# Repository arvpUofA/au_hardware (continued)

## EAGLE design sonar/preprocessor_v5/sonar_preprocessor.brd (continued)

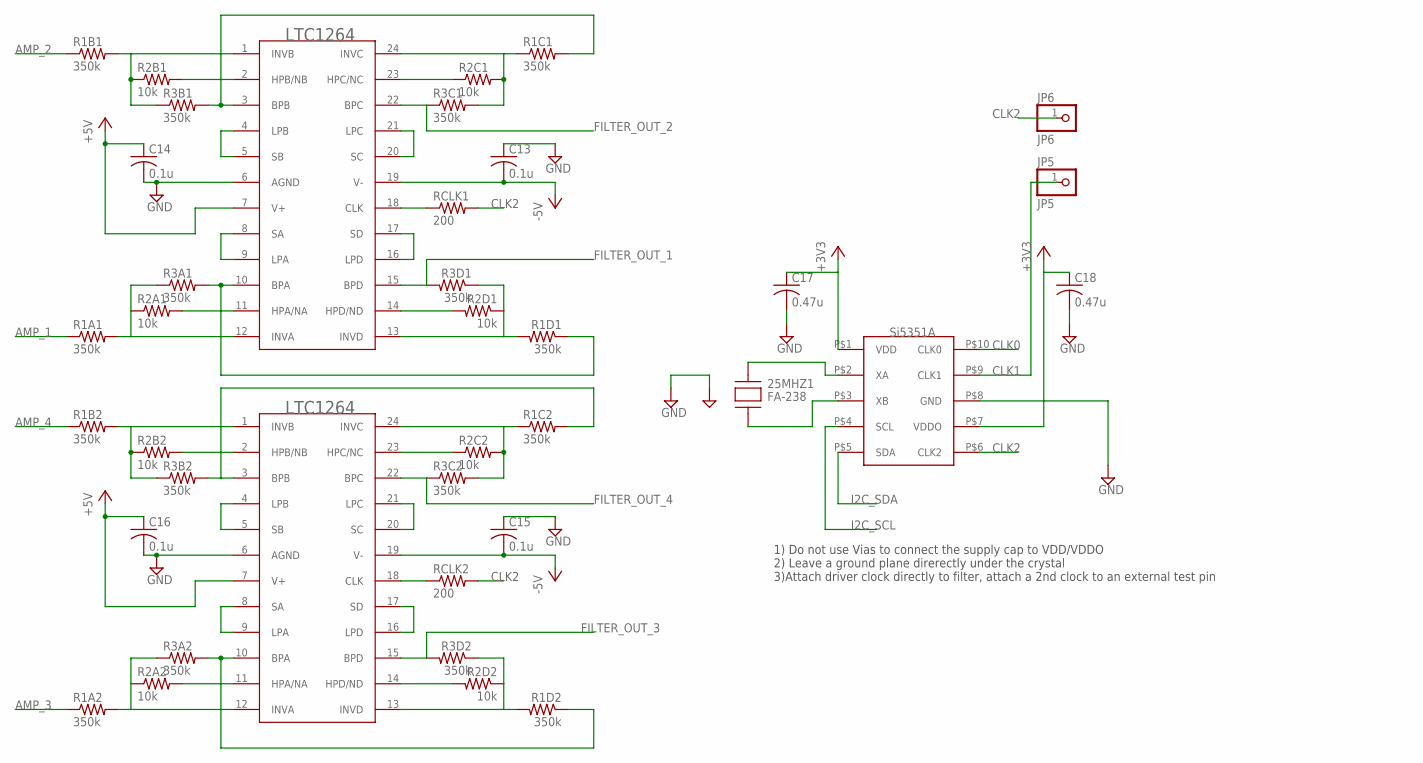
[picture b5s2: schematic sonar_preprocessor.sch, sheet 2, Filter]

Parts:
25MHZ1: FA-238
C13, C14, C15, C16: 0.1u; C0805
C17, C18: 0.47u; C0805
JP5: JP5; 1X01
JP6: JP6; 1X01
R1A1, R1A2, R1B1, R1B2, R1C1, R1C2, R1D1, R1D2, R3A1, R3A2, R3B1, R3B2, R3C1, R3C2, R3D1, R3D2: 350k; R0805
R2A1, R2A2, R2B1, R2B2, R2C1, R2C2, R2D1, R2D2: 10k; R0805
RCLK1, RCLK2: 200; R0805
U$6, U$7: LTC1264SMD; SO24W
U$8: SI5351A; MSOP-10

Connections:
+3V3: C17.1, C18.1, U$8.P$1 (VDD), U$8.P$7 (VDDO); also elsewhere on the board
+5V: C14.1, C16.1, U$6.7 (V+), U$7.7 (V+); also elsewhere on the board
-5V: C13.2, C15.2, U$6.19 (V-), U$7.19 (V-); also elsewhere on the board
AMP_1: R1A1.1; also elsewhere on the board
AMP_2: R1B1.1; also elsewhere on the board
AMP_3: R1A2.1; also elsewhere on the board
AMP_4: R1B2.1; also elsewhere on the board
CLK0: U$8.P$10 (CLK0)
CLK1: JP5.1, U$8.P$9 (CLK1)
CLK2: JP6.1, RCLK1.2, RCLK2.2, U$8.P$6 (CLK2)
FILTER_OUT_1: R3D1.2, U$6.15 (BPD); also elsewhere on the board
FILTER_OUT_2: R3C1.1, U$6.22 (BPC); also elsewhere on the board
FILTER_OUT_3: R3D2.2, U$7.15 (BPD); also elsewhere on the board
FILTER_OUT_4: R3C2.1, U$7.22 (BPC); also elsewhere on the board
GND: 25MHZ1.P$1 (GND), 25MHZ1.P$3 (GND), C13.1, C14.2, C15.1, C16.2, C17.2, C18.2, U$6.6 (AGND), U$7.6 (AGND), U$8.P$8 (GND); also elsewhere on the board
I2C_SCL: U$8.P$4 (SCL); also elsewhere on the board
I2C_SDA: U$8.P$5 (SDA); also elsewhere on the board
unnamed: U$7.20 (SC), U$7.21 (LPC)
unnamed: 25MHZ1.P$4 (XA), U$8.P$2 (XA)
unnamed: 25MHZ1.P$2 (XB), U$8.P$3 (XB)
unnamed: R2A1.2, U$6.11 (HPA/NA)
unnamed: U$6.8 (SA), U$6.9 (LPA)
unnamed: R1A1.2, R2A1.1, R3A1.1, U$6.12 (INVA)
unnamed: R2D1.2, U$6.14 (HPD/ND)
unnamed: R1D1.2, R2D1.1, R3D1.1, U$6.13 (INVD)
unnamed: U$6.16 (LPD), U$6.17 (SD)
unnamed: R2C1.1, U$6.23 (HPC/NC)
unnamed: R1C1.1, R2C1.2, R3C1.2, U$6.24 (INVC)
unnamed: R2C2.1, U$7.23 (HPC/NC)
unnamed: R2B1.2, U$6.2 (HPB/NB)
unnamed: R1B1.2, R2B1.1, R3B1.1, U$6.1 (INVB)
unnamed: U$6.4 (LPB), U$6.5 (SB)
unnamed: U$6.20 (SC), U$6.21 (LPC)
unnamed: RCLK1.1, U$6.18 (CLK)
unnamed: R2A2.2, U$7.11 (HPA/NA)
unnamed: U$7.8 (SA), U$7.9 (LPA)
unnamed: R1A2.2, R2A2.1, R3A2.1, U$7.12 (INVA)
unnamed: R2D2.2, U$7.14 (HPD/ND)
unnamed: R1D2.2, R2D2.1, R3D2.1, U$7.13 (INVD)
unnamed: U$7.16 (LPD), U$7.17 (SD)
unnamed: R1C2.1, R2C2.2, R3C2.2, U$7.24 (INVC)
unnamed: R2B2.2, U$7.2 (HPB/NB)
unnamed: R1B2.2, R2B2.1, R3B2.1, U$7.1 (INVB)
unnamed: U$7.4 (LPB), U$7.5 (SB)
unnamed: RCLK2.1, U$7.18 (CLK)
OUT_2ND_A1: R1D1.1, R3A1.2, U$6.10 (BPA)
OUT_2ND_A2: R1D2.1, R3A2.2, U$7.10 (BPA)
OUT_2ND_B2: R1C2.2, R3B2.2, U$7.3 (BPB)
OUT_2ND_ORDER_B1: R1C1.2, R3B1.2, U$6.3 (BPB)

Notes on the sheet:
1) Do not use Vias to connect the supply cap to VDD/VDDO 2) Leave a ground plane direrectly under the crystal 3)Attach driver clock directly to filter, attach a 2nd clock to an external test pin

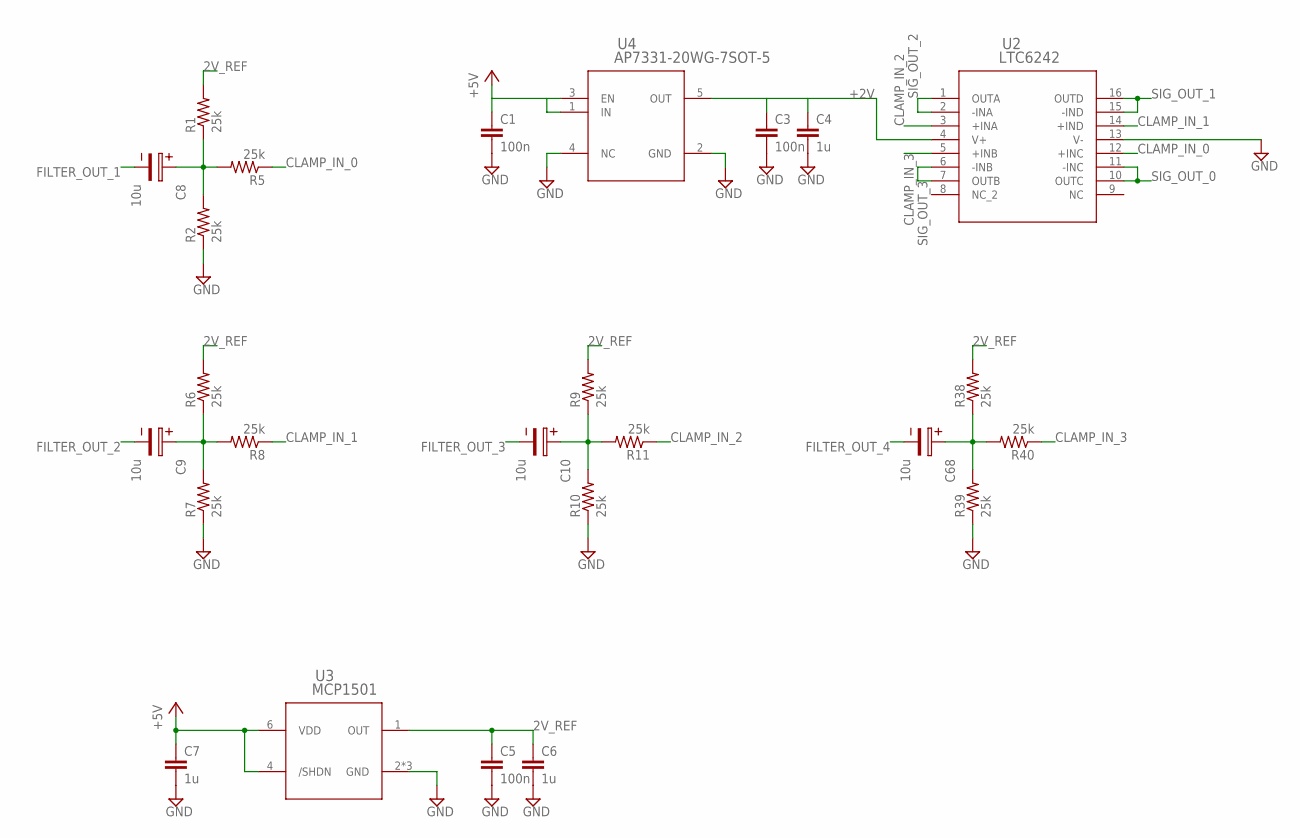
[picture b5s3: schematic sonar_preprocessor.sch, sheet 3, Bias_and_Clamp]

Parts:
C1, C3, C5: 100n; C0805
C4, C6, C7: 1u; C0805
C8, C9, C10, C68: 10u; 2.6X1.6X1(BXCXA)
R1, R2, R5, R6, R7, R8, R9, R10, R11, R38, R39, R40: 25k; R0805
U2: LTC6242; SSOP16
U3: MCP1501; SOT23-6
U4: AP7331-20WG-7SOT-5; SOT23-5

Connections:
2V_REF: C5.1, C6.1, R1.2, R6.2, R9.2, R38.2, U3.1 (OUT)
+2V: C3.1, C4.1, U2.4 (V+), U4.5 (OUT)
+5V: C1.1, C7.1, U3.4 (/SHDN), U3.6 (VDD), U4.1 (IN), U4.3 (EN); also elsewhere on the board
BIASED_0: C8.1, R1.1, R2.2, R5.2
BIASED_1: C9.1, R6.1, R7.2, R8.2
BIASED_2: C10.1, R9.1, R10.2, R11.2
BIASED_3: C68.1, R38.1, R39.2, R40.2
CLAMP_IN_0: R5.1, U2.12 (+INC)
CLAMP_IN_1: R8.1, U2.14 (+IND)
CLAMP_IN_2: R11.1, U2.3 (+INA)
CLAMP_IN_3: R40.1, U2.5 (+INB)
FILTER_OUT_1: C8.2; also elsewhere on the board
FILTER_OUT_2: C9.2; also elsewhere on the board
FILTER_OUT_3: C10.2; also elsewhere on the board
FILTER_OUT_4: C68.2; also elsewhere on the board
GND: C1.2, C3.2, C4.2, C5.2, C6.2, C7.2, R2.1, R7.1, R10.1, R39.1, U2.13 (V-), U3.2 (GND), U3.3 (GND), U3.5 (GND), U4.2 (GND), U4.4 (NC); also elsewhere on the board
SIG_OUT_0: U2.10 (OUTC), U2.11 (-INC); also elsewhere on the board
SIG_OUT_1: U2.15 (-IND), U2.16 (OUTD); also elsewhere on the board
SIG_OUT_2: U2.1 (OUTA), U2.2 (-INA); also elsewhere on the board
SIG_OUT_3: U2.6 (-INB), U2.7 (OUTB); also elsewhere on the board

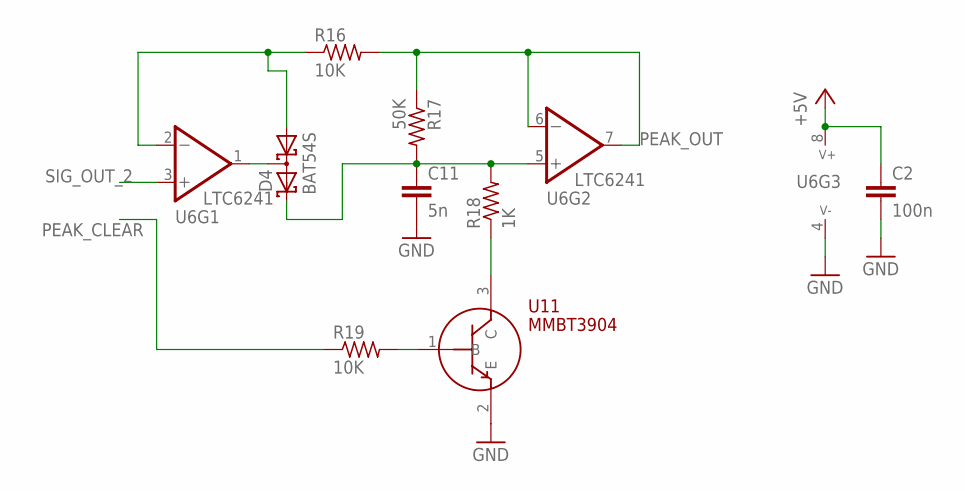
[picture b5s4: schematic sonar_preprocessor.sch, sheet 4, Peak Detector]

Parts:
C2: 100n; C0805
C11: 5n; C0805
D4: BAT54S; SOT23
R16, R19: 10K; R0805
R17: 50K; R0805
R18: 1K; R0805
U6: LTC6241; SO-8
U11: MMBT3904; SOT23

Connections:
+5V: C2.1, U6.8 (V+); also elsewhere on the board
GND: C2.2, C11.2, U6.4 (V-), U11.2 (E); also elsewhere on the board
unnamed: C11.1, D4.2 (C2), R17.2, R18.2, U6.5 (+IN)
unnamed: D4.1 (A1), R16.1, U6.2 (-IN)
unnamed: D4.3 (C1A2), U6.1 (OUT)
unnamed: R19.2, U11.1 (B)
unnamed: R18.1, U11.3 (C)
PEAK_CLEAR: R19.1; also elsewhere on the board
PEAK_OUT: R16.2, R17.1, U6.6 (-IN), U6.7 (OUT); also elsewhere on the board
SIG_OUT_2: U6.3 (+IN); also elsewhere on the board

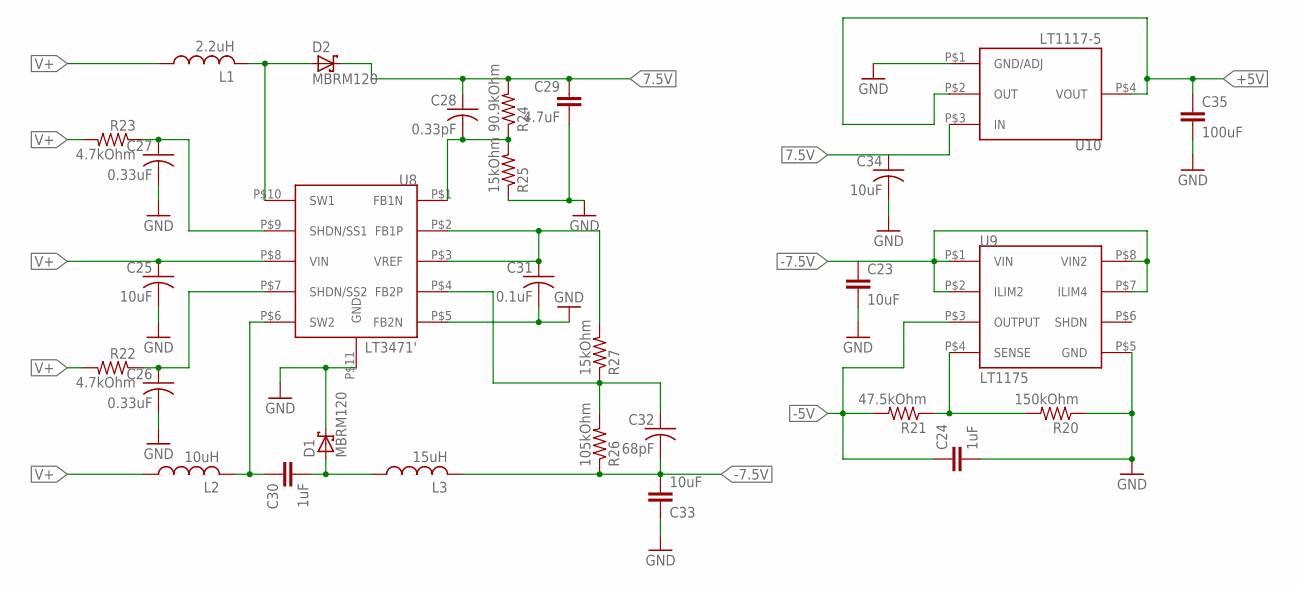
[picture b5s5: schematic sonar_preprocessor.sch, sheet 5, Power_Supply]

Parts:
C23, C33: 10uF; C0805
C24, C30: 1uF; C1206
C25, C34: 10uF; C0603
C26, C27: 0.33uF; C0603
C28: 0.33pF; C0603
C29: 4.7uF; C1206
C31: 0.1uF; C0603
C32: 68pF; C0603
C35: 100uF; C1210
D1, D2: MBRM120; DO-216AA
L1: 2.2uH; NS4.9X4.9
L2: 10uH; NS5X5
L3: 15uH; NS5X5
R20: 150kOhm; R0603
R21: 47.5kOhm; R0603
R22, R23: 4.7kOhm; R0603
R24: 90.9kOhm; R0603
R25, R27: 15kOhm; R0603
R26: 105kOhm; R0603
U8: LT3471'; 10-WFDFN
U9: LT1175; 8-SOIC
U10: LT1117-5; SOT233-3

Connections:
7.5V: C28.1, C29.1, C34.1, D2.P$1 (C), R24.2, U10.P$3 (IN)
+5V: C35.1, U10.P$2 (OUT), U10.P$4 (VOUT); also elsewhere on the board
-5V: C24.1, R21.2, U9.P$3 (OUTPUT); also elsewhere on the board
-7.5V: C23.1, C32.2, C33.2, L3.P$2 (2), R26.1, U9.P$1 (VIN), U9.P$2 (ILIM2), U9.P$7 (ILIM4), U9.P$8 (VIN2)
GND: C23.2, C24.2, C25.2, C26.2, C27.2, C29.2, C31.2, C33.1, C34.2, C35.2, D1.P$1 (C), R20.1, R25.1, U8.P$5 (FB2N), U8.P$11 (GND), U9.P$5 (GND), U10.P$1 (GND/ADJ); also elsewhere on the board
unnamed: R20.2, R21.1, U9.P$4 (SENSE)
unnamed: D2.P$2 (A), L1.P$2 (2), U8.P$10 (SW1)
unnamed: C28.2, R24.1, R25.2, U8.P$1 (FB1N)
unnamed: C30.1, L2.P$2 (2), U8.P$6 (SW2)
unnamed: C30.2, D1.P$2 (A), L3.P$1 (1)
unnamed: C32.1, R26.2, R27.1, U8.P$4 (FB2P)
SS3: C26.1, R22.1, U8.P$7 (SHDN/SS2)
SS4: C27.1, R23.1, U8.P$9 (SHDN/SS1)
V+: C25.1, L1.P$1 (1), L2.P$1 (1), R22.2, R23.2, U8.P$8 (VIN); also elsewhere on the board
VREF: C31.1, R27.2, U8.P$2 (FB1P), U8.P$3 (VREF)

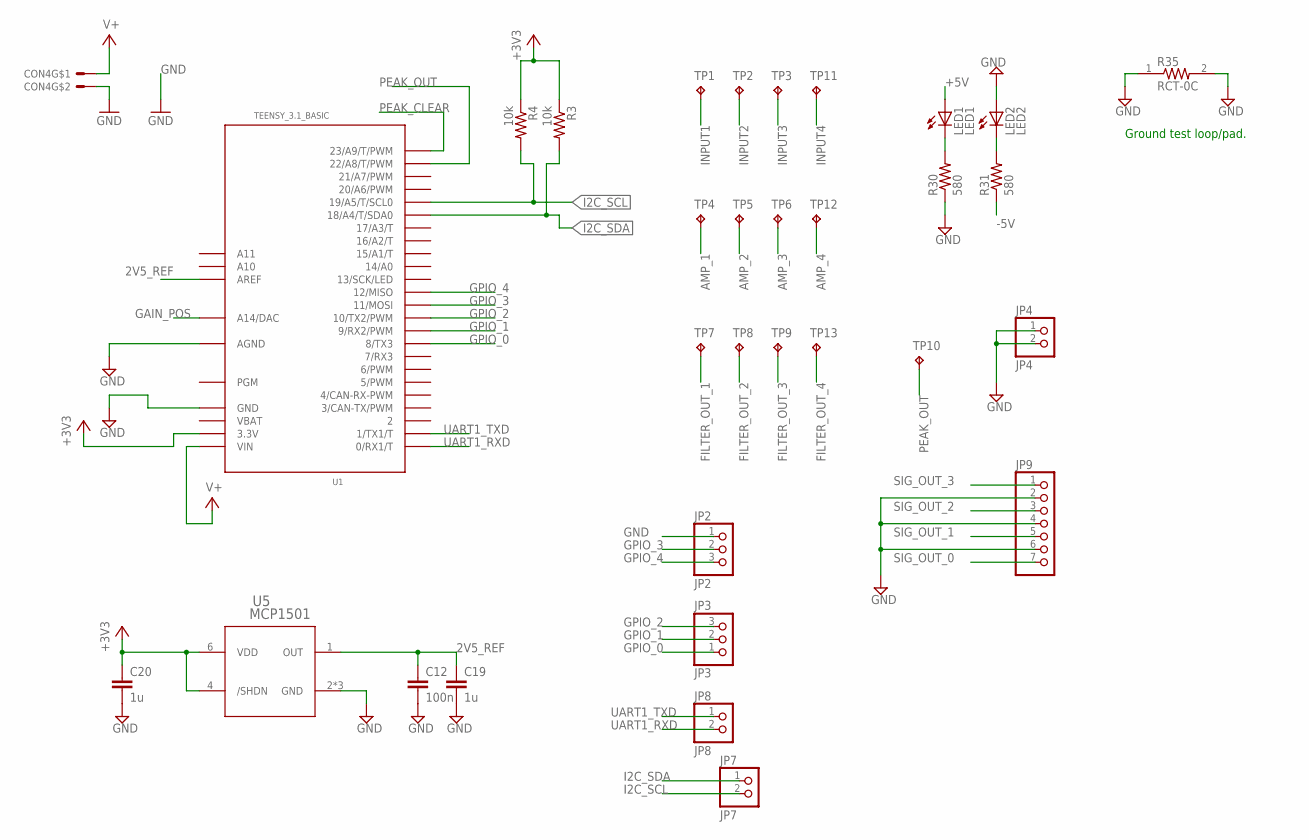
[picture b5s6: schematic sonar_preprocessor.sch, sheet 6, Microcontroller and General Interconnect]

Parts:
C12: 100n; C0805
C19, C20: 1u; C0805
CON4: MOLEX_5566-2; 5566-2
JP2: JP2; 1X03SMD/90
JP3: JP3; 1X03SMD/90
JP4: JP4; 1X02
JP7: JP7; 1X02
JP8: JP8; 1X02SMD/90
JP9: PINHD-1X7/90; 1X07/90
LED1: LED1; SML0805
LED2: LED2; SML0805
R3, R4: 10k; R0805
R30, R31: 580; R0805
R35: RCT-0C; RESC2012X65N
TP1, TP2, TP3, TP4, TP5, TP6, TP7, TP8, TP9, TP10, TP11, TP12, TP13: TPB2,54; B2,54
U1: TEENSY_3.1_BASIC
U5: MCP1501; SOT23-6

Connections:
2V5_REF: C12.1, C19.1, U1.AREF, U5.1 (OUT)
+3V3: C20.1, R3.1, R4.1, U1.3.3V, U1.3.3V1 (3.3V), U5.4 (/SHDN), U5.6 (VDD); also elsewhere on the board
+5V: LED1.A; also elsewhere on the board
-5V: R31.1; also elsewhere on the board
AMP_1: TP4.TP; also elsewhere on the board
AMP_2: TP5.TP; also elsewhere on the board
AMP_3: TP6.TP; also elsewhere on the board
AMP_4: TP12.TP; also elsewhere on the board
FILTER_OUT_1: TP7.TP; also elsewhere on the board
FILTER_OUT_2: TP8.TP; also elsewhere on the board
FILTER_OUT_3: TP9.TP; also elsewhere on the board
FILTER_OUT_4: TP13.TP; also elsewhere on the board
GAIN_POS: U1.A14 (A14/DAC); also elsewhere on the board
GND: C12.2, C19.2, C20.2, CON4.2, JP2.1, JP4.1, JP4.2, JP9.2, JP9.4, JP9.6, LED2.A, R30.1, R35.1, R35.2, U1.AGND, U1.GND, U1.GND1 (GND), U5.2 (GND), U5.3 (GND), U5.5 (GND); also elsewhere on the board
GPIO_0: JP3.1, U1.8 (8/TX3)
GPIO_1: JP3.2, U1.9 (9/RX2/PWM)
GPIO_2: JP3.3, U1.10 (10/TX2/PWM)
GPIO_3: JP2.2, U1.11 (11/MOSI)
GPIO_4: JP2.3, U1.12 (12/MISO)
I2C_SCL: JP7.2, R4.2, U1.19/A5 (19/A5/T/SCL0); also elsewhere on the board
I2C_SDA: JP7.1, R3.2, U1.18/A4 (18/A4/T/SDA0); also elsewhere on the board
INPUT1: TP1.TP; also elsewhere on the board
INPUT2: TP2.TP; also elsewhere on the board
unnamed: LED2.C, R31.2
unnamed: LED1.C, R30.2
PEAK_CLEAR: U1.23/A9 (23/A9/T/PWM); also elsewhere on the board
PEAK_OUT: TP10.TP, U1.22/A8 (22/A8/T/PWM); also elsewhere on the board
SIG_OUT_0: JP9.7; also elsewhere on the board
SIG_OUT_1: JP9.5; also elsewhere on the board
SIG_OUT_2: JP9.3; also elsewhere on the board
SIG_OUT_3: JP9.1; also elsewhere on the board
UART1_RXD: JP8.2, U1.0 (0/RX1/T)
UART1_TXD: JP8.1, U1.1 (1/TX1/T)
V+: CON4.1, U1.VIN; also elsewhere on the board
VBAT: U1.VBAT

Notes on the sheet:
Ground test loop/pad.

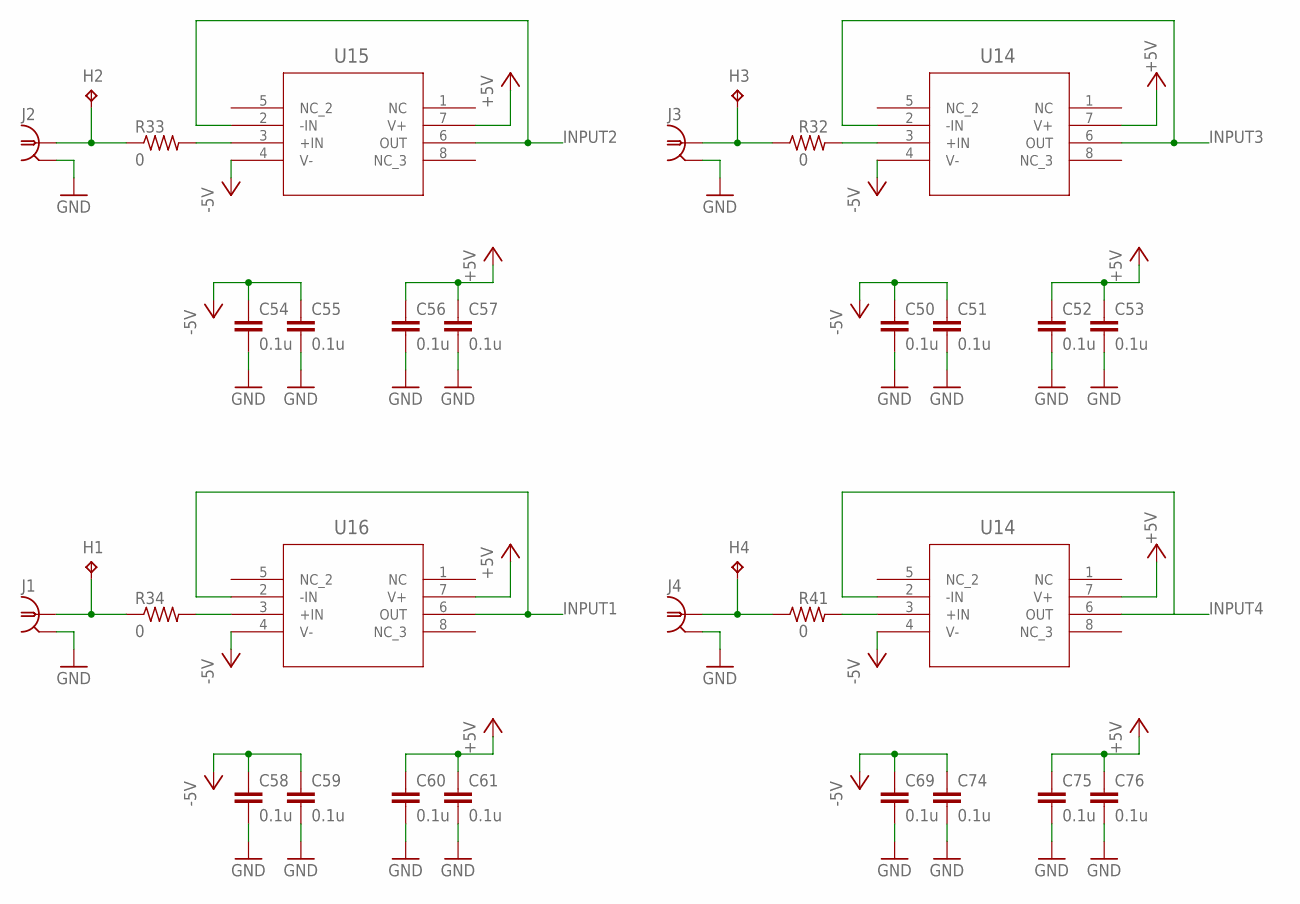
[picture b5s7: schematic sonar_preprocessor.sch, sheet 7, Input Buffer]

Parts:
C50, C51, C52, C53, C54, C55, C56, C57, C58, C59, C60, C61, C69, C74, C75, C76: 0.1u; C0603
H1, H2, H3, H4: TPB2,54; B2,54
J1, J2, J3, J4: TE_5-1634503-1TE; TE_5-1634503-1
R32, R33, R34, R41: 0; R0603
U14, U19: U14; SO-8
U15: U15; SO-8
U16: U16; SO-8

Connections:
+5V: C52.1, C53.1, C56.1, C57.1, C60.1, C61.1, C75.1, C76.1, U14.7 (V+), U15.7 (V+), U16.7 (V+), U19.7 (V+); also elsewhere on the board
-5V: C50.1, C51.1, C54.1, C55.1, C58.1, C59.1, C69.1, C74.1, U14.4 (V-), U15.4 (V-), U16.4 (V-), U19.4 (V-); also elsewhere on the board
GND: C50.2, C51.2, C52.2, C53.2, C54.2, C55.2, C56.2, C57.2, C58.2, C59.2, C60.2, C61.2, C69.2, C74.2, C75.2, C76.2, J1.2, J1.3 (2), J1.4 (2), J1.5 (2), J2.2, J2.3 (2), J2.4 (2), J2.5 (2), J3.2, J3.3 (2), J3.4 (2), J3.5 (2), J4.2, J4.3 (2), J4.4 (2), J4.5 (2); also elsewhere on the board
INPUT1: U16.2 (-IN), U16.6 (OUT); also elsewhere on the board
INPUT2: U15.2 (-IN), U15.6 (OUT); also elsewhere on the board
unnamed: H4.TP, J4.1, R41.1
unnamed: H3.TP, J3.1, R32.1
unnamed: R32.2, U14.3 (+IN)
unnamed: H2.TP, J2.1, R33.1
unnamed: R33.2, U15.3 (+IN)
unnamed: R34.2, U16.3 (+IN)
unnamed: H1.TP, J1.1, R34.1
unnamed: R41.2, U19.3 (+IN)

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
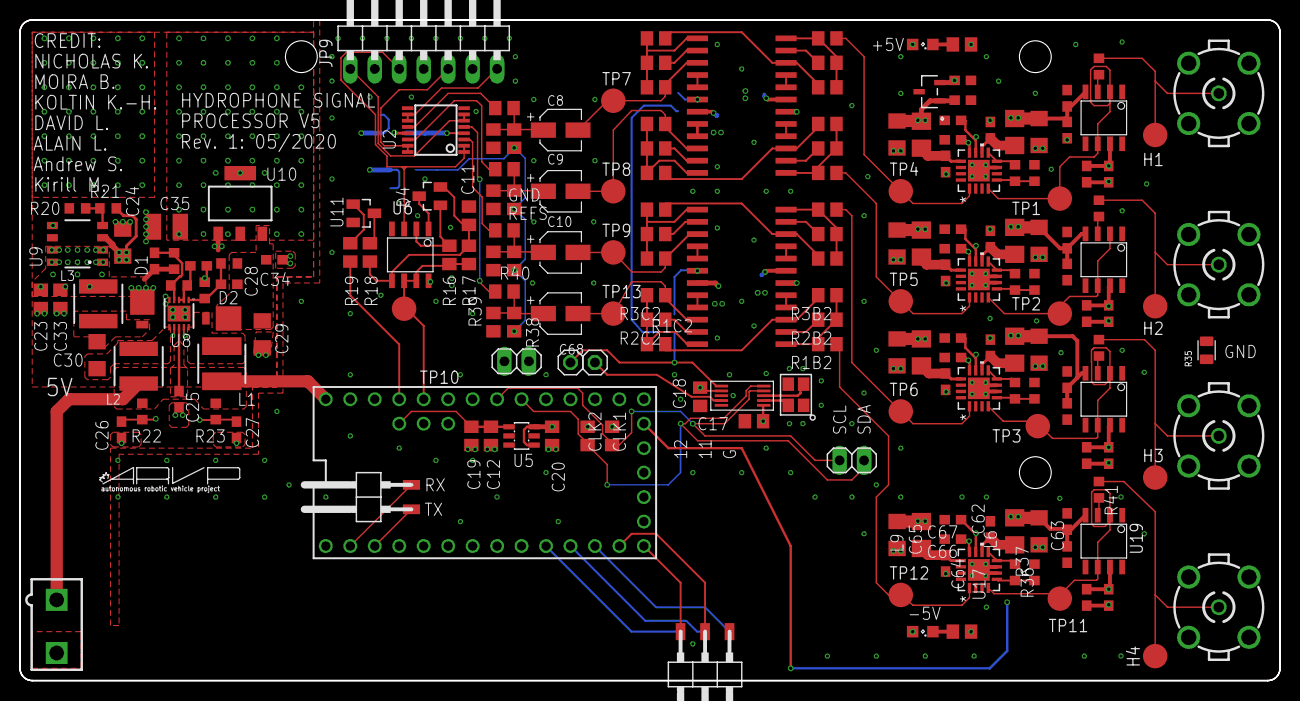
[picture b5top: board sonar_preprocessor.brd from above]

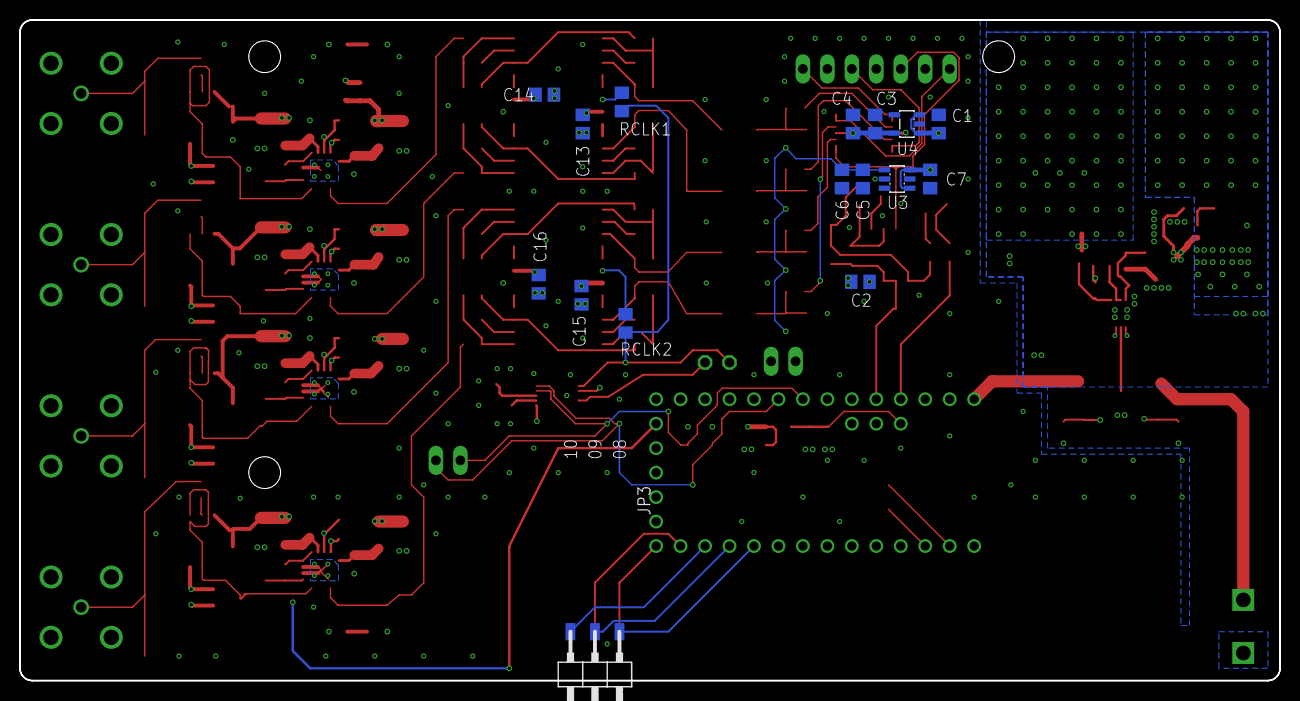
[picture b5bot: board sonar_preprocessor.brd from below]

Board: 4 copper layers, 130.8 x 68.6 mm, 217 parts (16 on the bottom side), 121 nets.

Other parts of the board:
U$1: A4L-LOC
U$2, U$3, U$5: STAND-OFF
U$4: ARVP

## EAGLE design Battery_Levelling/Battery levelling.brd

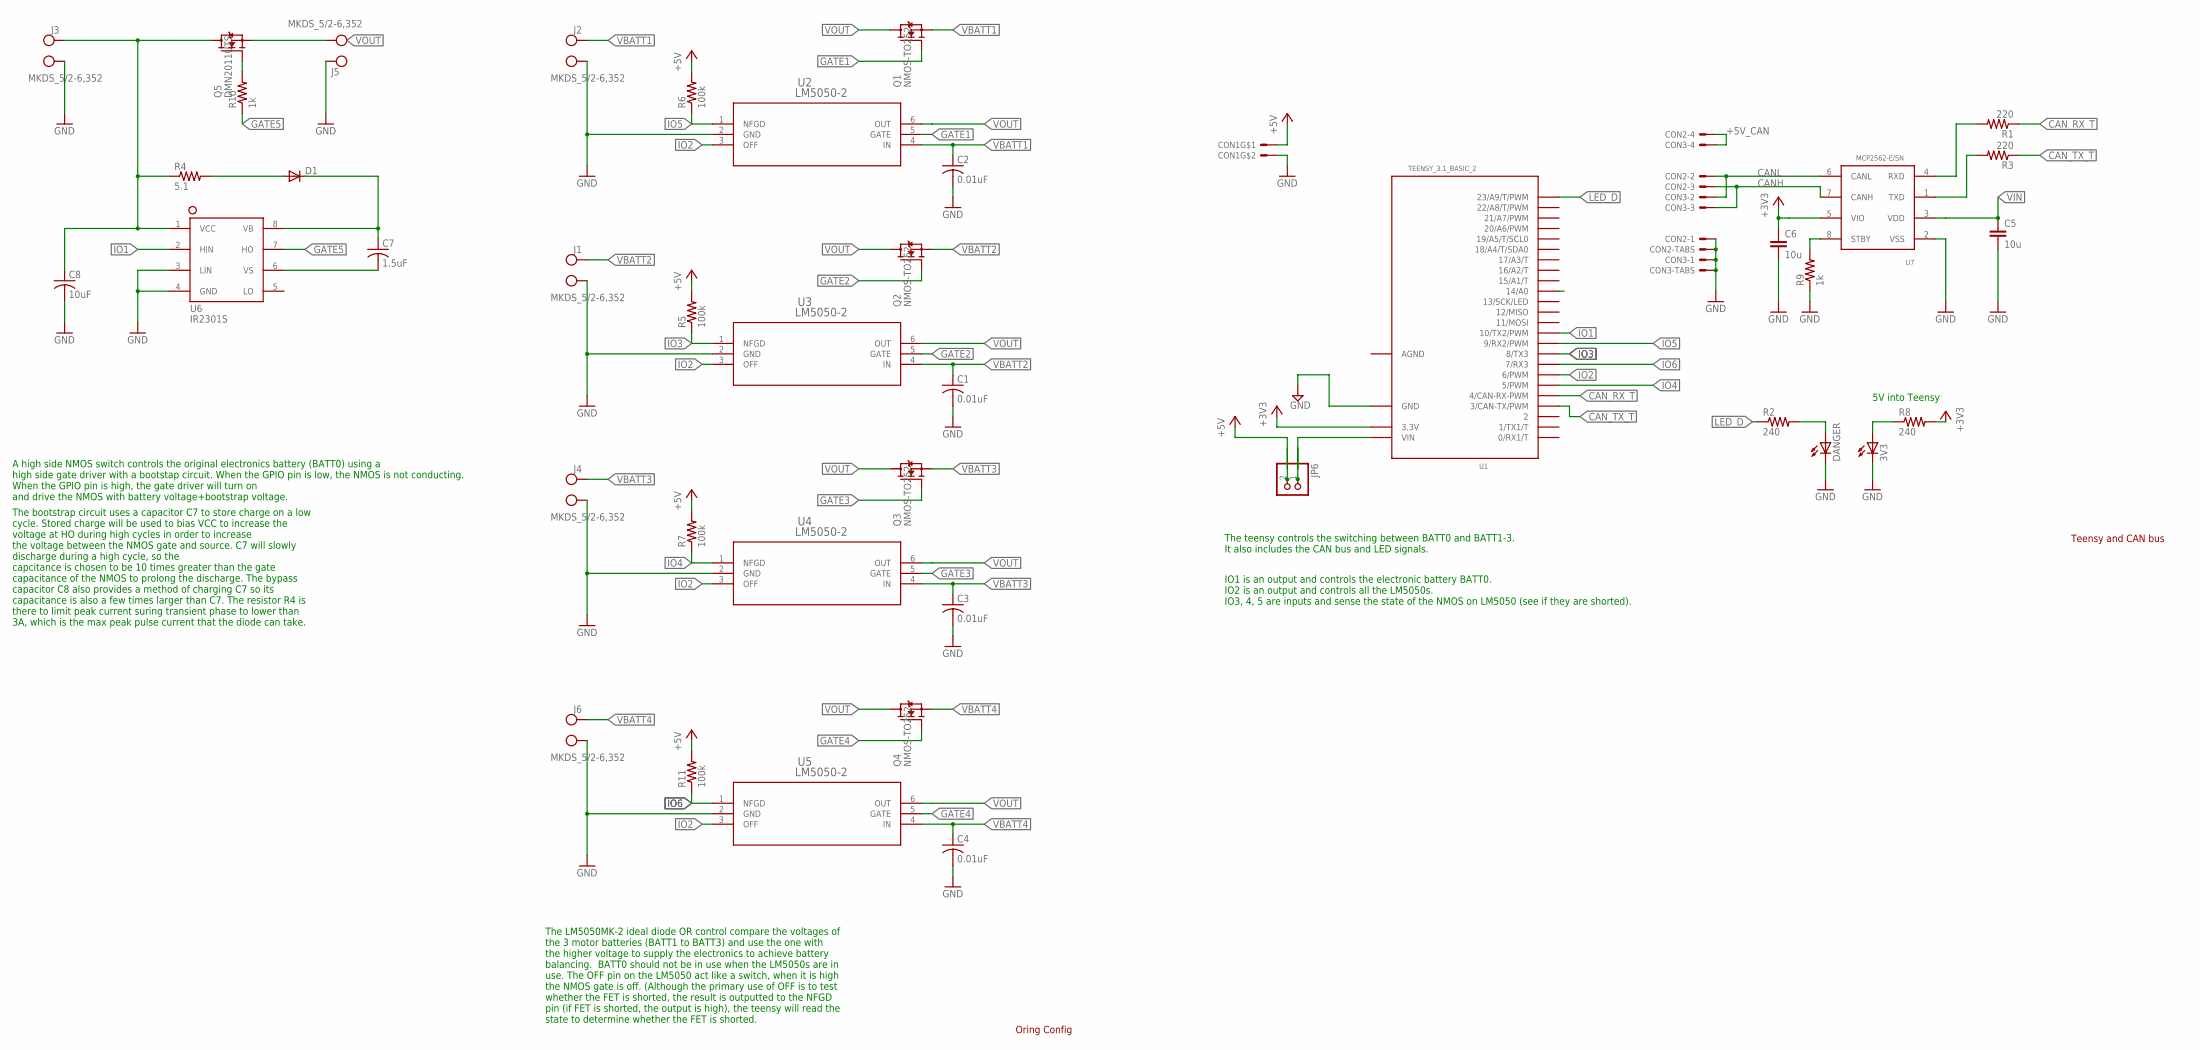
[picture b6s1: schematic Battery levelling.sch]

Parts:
3V3: LEDSMT1206; 1206
C1, C2, C3, C4: 0.01uF; C0805
C5, C6: 10u; C0805
C7: 1.5uF; C0805
C8: 10uF; C1206
CON1: MOLEX_5566-2; 5566-2
CON2, CON3: SM04B-GHS-TB
D1: DIODE-DO-214AC; DO-214AC
DANGER: LEDSMT1206; 1206
J1, J2, J3, J4, J5, J6: MKDS_5/2-6,352; MKDS_5/2-6,35
JP6: PINHD-1X2; 1X02
Q1, Q2, Q3, Q4: NMOS-TO252; TO252
Q5: DMN2011UTS; SOP65P640X120-8N
R1, R3: 220; R0805
R2, R8: 240; R1206
R4: 5.1; R1206
R5, R6, R7, R11: 100k; R1206
R9, R10: 1k; R0805
U1: TEENSY_3.1_BASIC_2
U2, U3, U4, U5: LM5050-2; MK06A
U6: IR2301S; SOIC8
U7: MCP2562-E/SN; SOIC8

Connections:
+3V3: C6.1, R8.2, U1.3.3V, U7.5 (VIO)
+5V: CON1.1, R5.2, R6.2, R7.2, R11.2
+5V1: JP6.2
+5V_CAN: CON2.P$4, CON3.P$4
AGND: U1.AGND
CANH: CON2.P$3, CON3.P$3, U7.7 (CANH)
CANL: CON2.P$2, CON3.P$2, U7.6 (CANL)
CAN_RX1: R1.2, U7.4 (RXD)
CAN_RX_T: R1.1, U1.4 (4/CAN-RX-PWM)
CAN_TX2: R3.2, U7.1 (TXD)
CAN_TX_T: R3.1, U1.3 (3/CAN-TX/PWM)
GATE1: Q1.1 (G), U2.5 (GATE)
GATE2: Q2.1 (G), U3.5 (GATE)
GATE3: Q3.1 (G), U4.5 (GATE)
GATE4: Q4.1 (G), U5.5 (GATE)
GATE5: R10.1, U6.7 (HO)
GND: 3V3.C, C1.2, C2.2, C3.2, C4.2, C5.2, C6.2, C8.2, CON1.2, CON2.P$1, CON2.P$5, CON2.P$6, CON3.P$1, CON3.P$5, CON3.P$6, DANGER.C, J1.1 (KL), J2.1 (KL), J3.1 (KL), J4.1 (KL), J5.2 (KL1), J6.1 (KL), R9.1, U1.GND, U2.2 (GND), U3.2 (GND), U4.2 (GND), U5.2 (GND), U6.3 (LIN), U6.4 (GND), U7.2 (VSS)
IO1: U1.10 (10/TX2/PWM), U6.2 (HIN)
IO2: U1.6 (6/PWM), U2.3 (OFF), U3.3 (OFF), U4.3 (OFF), U5.3 (OFF)
IO3: R5.1, U1.8 (8/TX3), U3.1 (NFGD)
IO4: R7.1, U1.5 (5/PWM), U4.1 (NFGD)
IO5: R6.1, U1.9 (9/RX2/PWM), U2.1 (NFGD)
IO6: R11.1, U1.7 (7/RX3), U5.1 (NFGD)
LEAK_IN: U1.14/A0
LED_D: R2.1, U1.23/A9 (23/A9/T/PWM)
unnamed: C8.1, J3.2 (KL1), Q5.5 (D), Q5.6 (D), Q5.7 (D), Q5.8 (D), R4.1, U6.1 (VCC)
unnamed: DANGER.A, R2.2
unnamed: D1.A, R4.2
unnamed: C7.2, U6.6 (VS)
unnamed: C7.1, D1.C, U6.8 (VB)
unnamed: Q5.4 (G), R10.2
unnamed: 3V3.A, R8.1
STB1: R9.2, U7.8 (STBY)
VBATT1: C2.1, J2.2 (KL1), Q1.3 (S), U2.4 (IN)
VBATT2: C1.1, J1.2 (KL1), Q2.3 (S), U3.4 (IN)
VBATT3: C3.1, J4.2 (KL1), Q3.3 (S), U4.4 (IN)
VBATT4: C4.1, J6.2 (KL1), Q4.3 (S), U5.4 (IN)
VIN: C5.1, U1.VIN, U7.3 (VDD)
VIN1: JP6.1
VOUT: J5.1 (KL), Q1.2 (D), Q2.2 (D), Q3.2 (D), Q4.2 (D), Q5.1 (S), Q5.2 (S), Q5.3 (S), U2.6 (OUT), U3.6 (OUT), U4.6 (OUT), U5.6 (OUT)

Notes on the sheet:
Teensy and CAN bus
5V into Teensy
Oring Config
A high side NMOS switch controls the original electronics battery (BATT0) using a high side gate driver with a bootstap circuit. When the GPIO pin is low, the NMOS is not conducting. When the GPIO pin is high, the gate driver will turn on and drive the NMOS with battery voltage+bootstrap voltage.
The LM5050MK-2 ideal diode OR control compare the voltages of the 3 motor batteries (BATT1 to BATT3) and use the one with the higher voltage to supply the electronics to achieve battery balancing. BATT0 should not be in use when the LM5050s are in use. The OFF pin on the LM5050 act like a switch, w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
The teensy controls the switching between BATT0 and BATT1-3. It also includes the CAN bus and LED signals.
IO1 is an output and controls the electronic battery BATT0. IO2 is an output and controls all the LM5050s. IO3, 4, 5 are inputs and sense the state of the NMOS on LM5050 (see if they are shorted).
The bootstrap circuit uses a capacitor C7 to store charge on a low cycle. Stored charge will be used to bias VCC to increase the voltage at HO during high cycles in order to increase the voltage between the NMOS gate and source. C7 will slowly discharge during a high cycle, so the capcitance is cho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

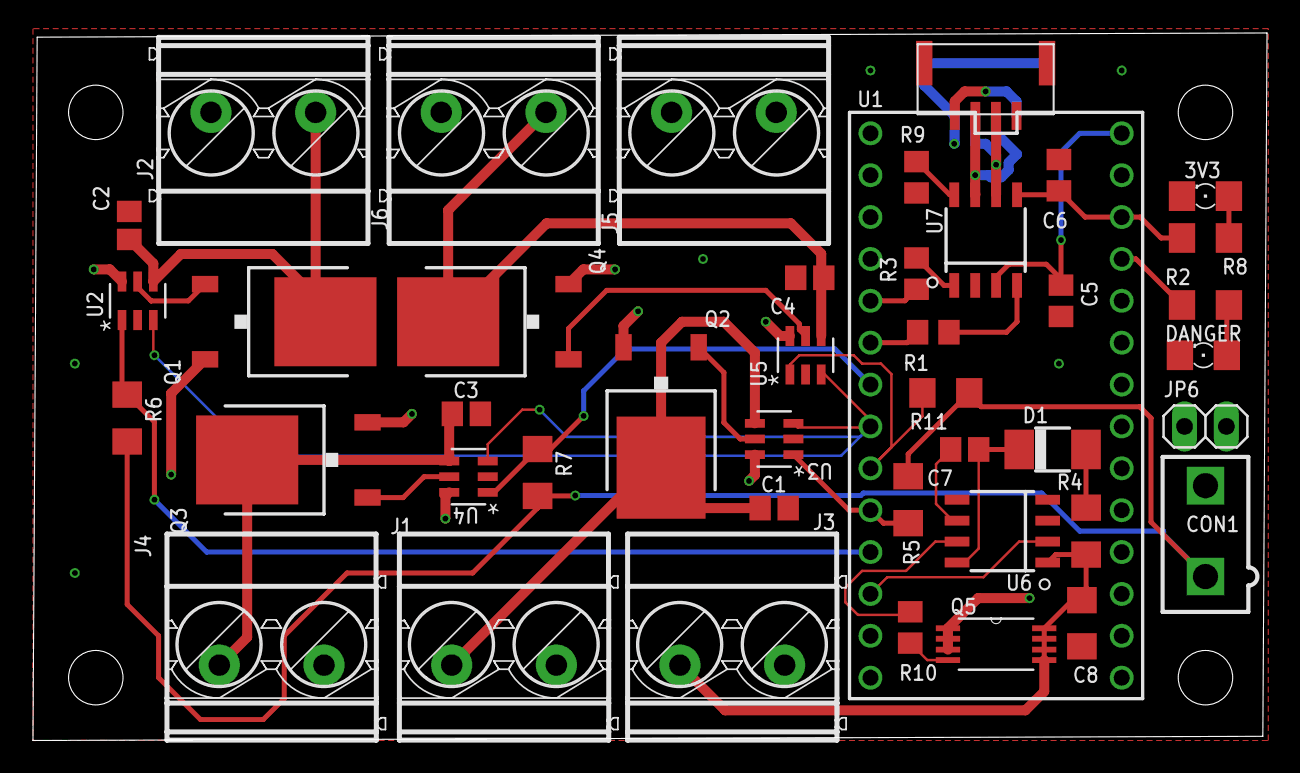
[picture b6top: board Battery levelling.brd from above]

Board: 2 copper layers, 74.9 x 42.9 mm, 48 parts (1 on the bottom side), 36 nets.

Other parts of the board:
U$1, U$2, U$3, U$4: STAND-OFF
